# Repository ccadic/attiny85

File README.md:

# attiny85
Dev board for ATTINY85
Opensource

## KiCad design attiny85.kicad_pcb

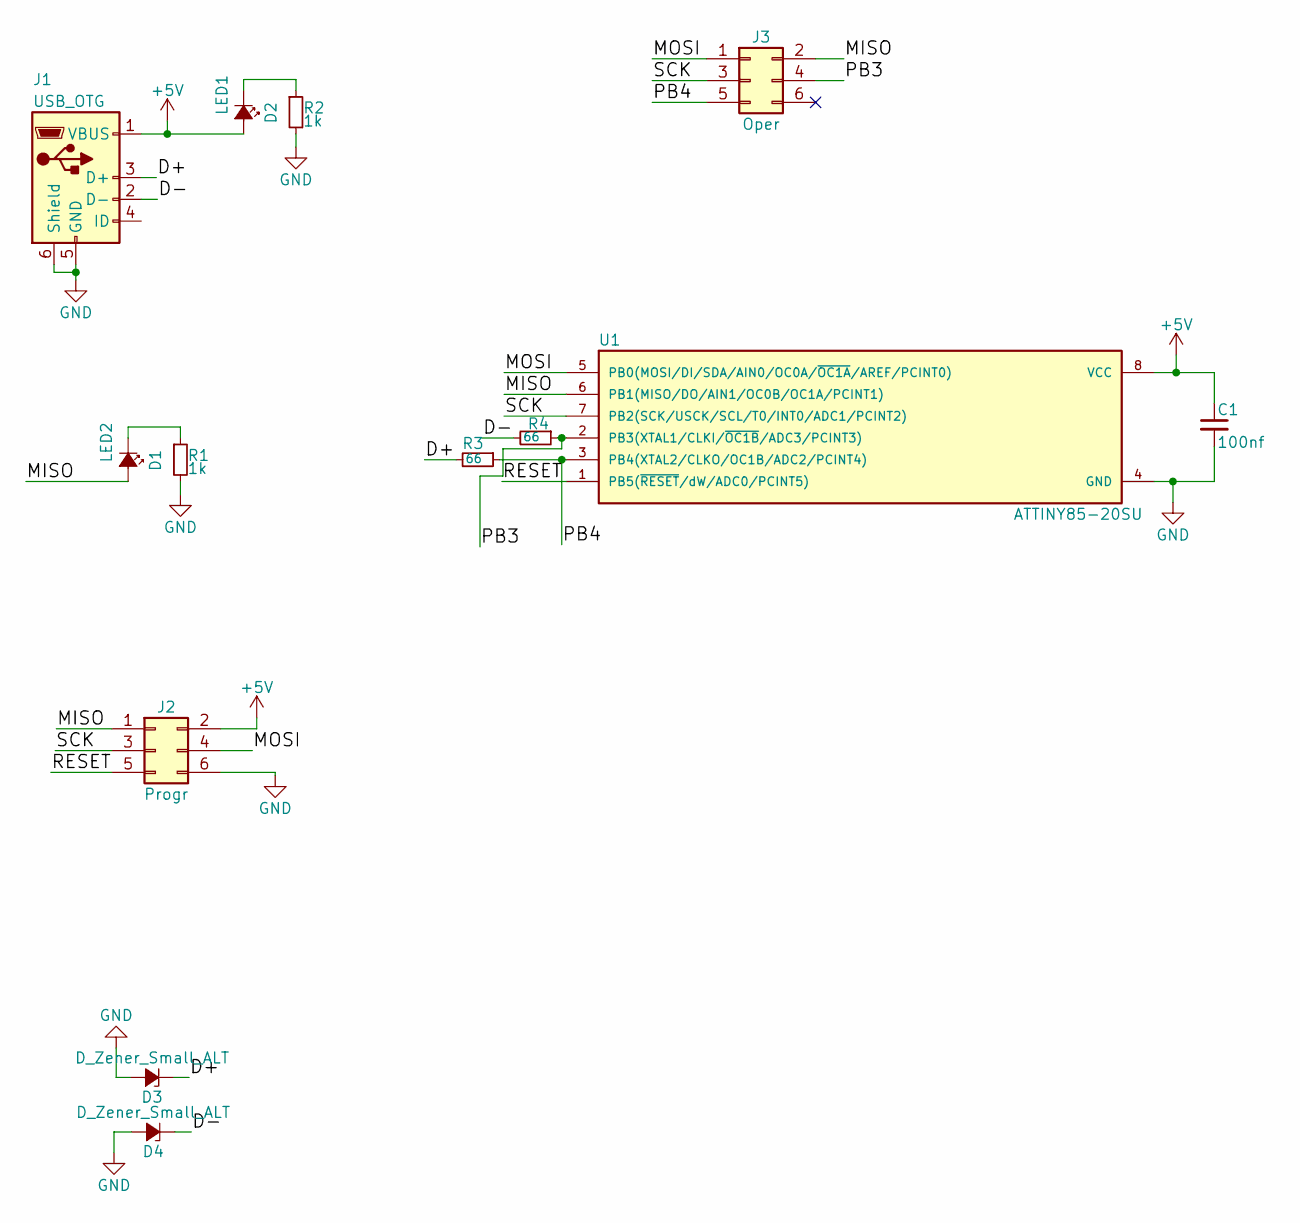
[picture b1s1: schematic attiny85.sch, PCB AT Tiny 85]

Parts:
C1: 100nf; C_1206_HandSoldering
D1: LED2; LED_1206_HandSoldering
D2: LED1; LED_1206_HandSoldering
D3, D4: D_Zener_Small_ALT; SOT-23
J1: USB_OTG; USB_Micro-B_Molex-105017-0001
J2: Progr; Socket_Strip_Straight_2x03_Pitch2.54mm
J3: Oper; Socket_Strip_Straight_2x03_Pitch2.54mm
R1: 1k; R_1206_HandSoldering
R2: 1k
R3, R4: 66; R_1206_HandSoldering
U1: ATTINY85-20SU; SOIC-8_3.9x4.9mm_Pitch1.27mm

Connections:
+5V: C1.1, D2.2 (A), J1.1 (VBUS), J2.2, U1.8 (VCC)
/D+: D3.1 (K), J1.3 (D+), R3.2
/D-: D4.1 (K), J1.2 (D-), R4.2
/MISO: D1.2 (A), J2.1, J3.2, U1.6 (PB1(MISO/DO/AIN1/OC0B/OC1A/PCINT1))
/MOSI: J2.4, J3.1, U1.5 (PB0(MOSI/DI/SDA/AIN0/OC0A/~OC1A~/AREF/P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)
/PB3: J3.4, R4.1, U1.2 (PB3(XTAL1/CLKI/~OC1B~/ADC3/PCINT3))
/PB4: J3.5, R3.1, U1.3 (PB4(XTAL2/CLKO/OC1B/ADC2/PCINT4))
/RESET: J2.5, U1.1 (PB5(~RESET~/dW/ADC0/PCINT5))
/SCK: J2.3, J3.3, U1.7 (PB2(SCK/USCK/SCL/T0/INT0/ADC1/PCINT2))
GND: C1.2, D3.2 (A), D4.2 (A), J1.5 (GND), J1.6 (Shield), J2.6, R1.2, R2.2, U1.4 (GND)
unnamed: D1.1 (K), R1.1
unnamed: D2.1 (K), R2.1

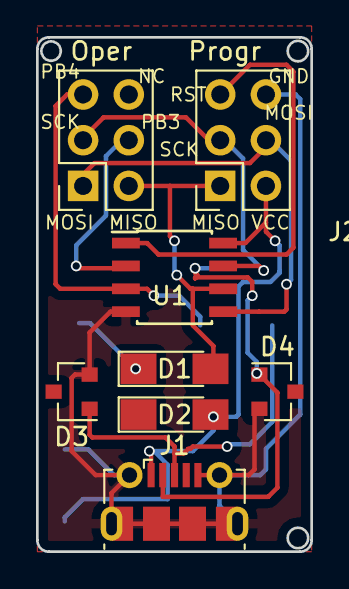
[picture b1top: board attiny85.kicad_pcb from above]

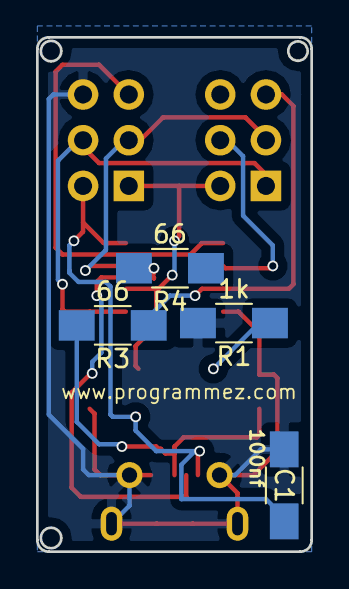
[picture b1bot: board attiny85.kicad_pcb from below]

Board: 2 copper layers, 15.2 x 28.6 mm, 12 parts (4 on the bottom side), 11 nets.
